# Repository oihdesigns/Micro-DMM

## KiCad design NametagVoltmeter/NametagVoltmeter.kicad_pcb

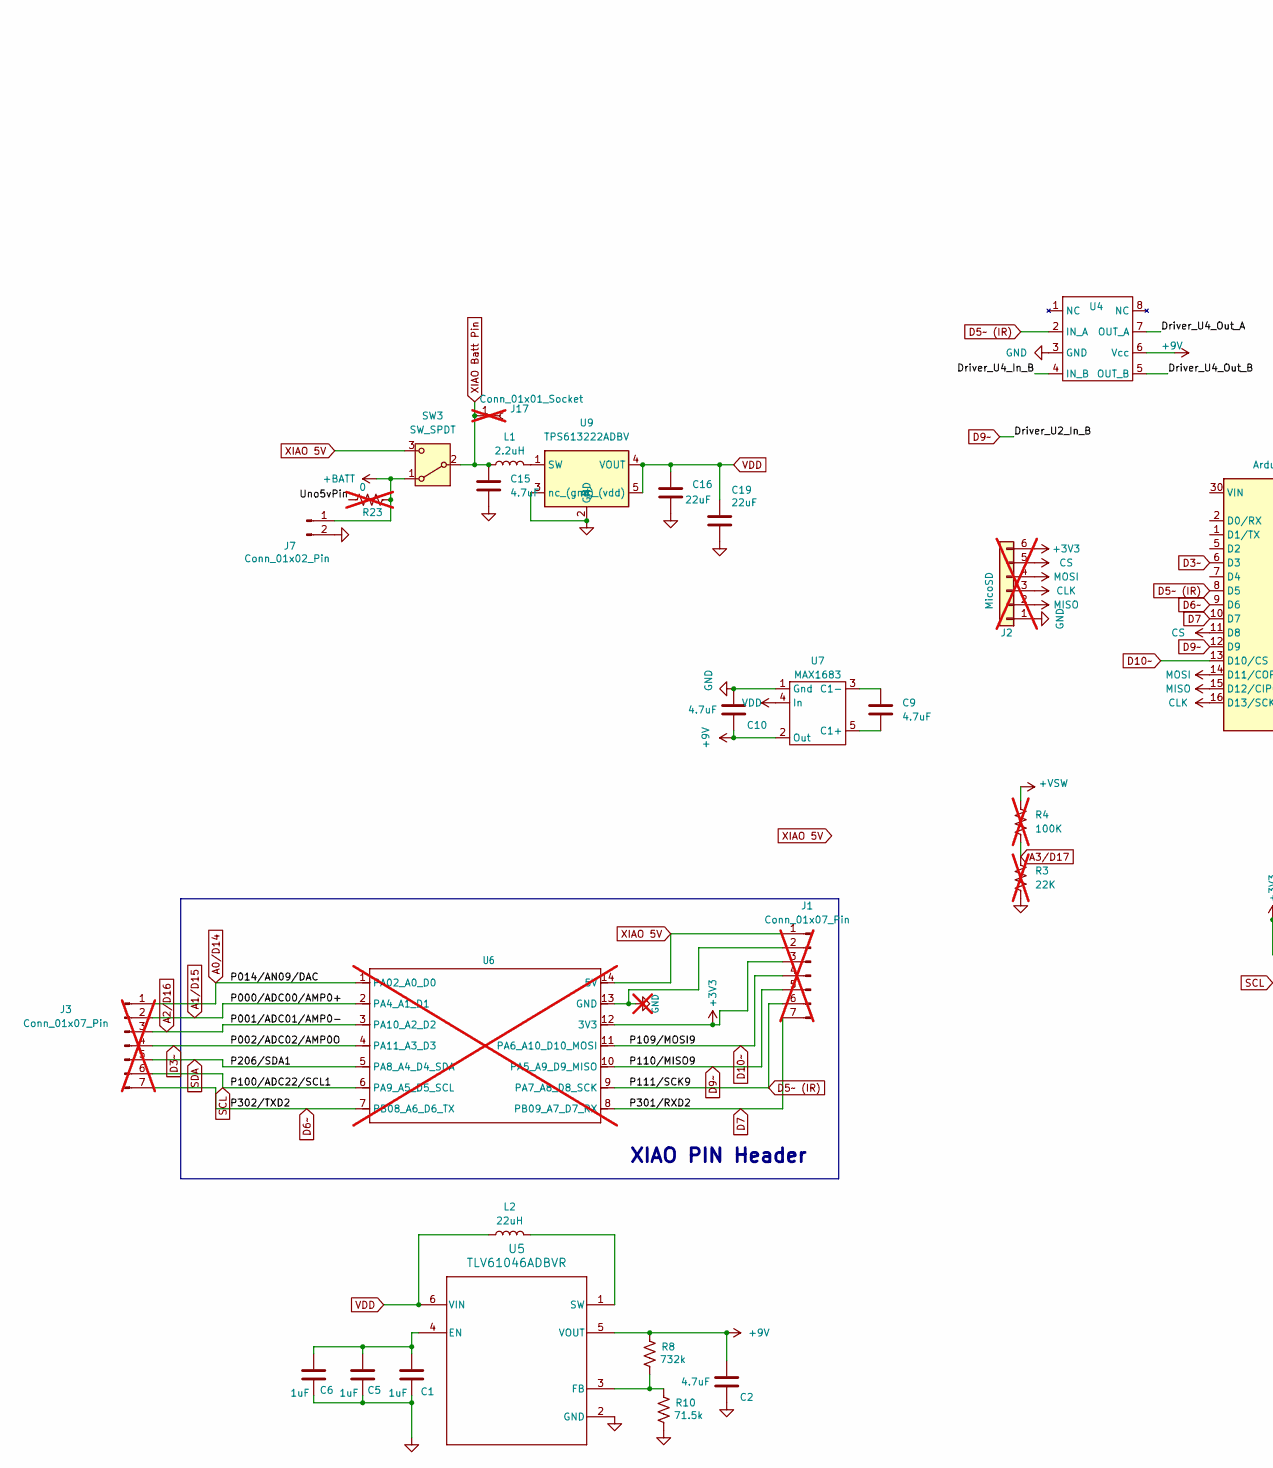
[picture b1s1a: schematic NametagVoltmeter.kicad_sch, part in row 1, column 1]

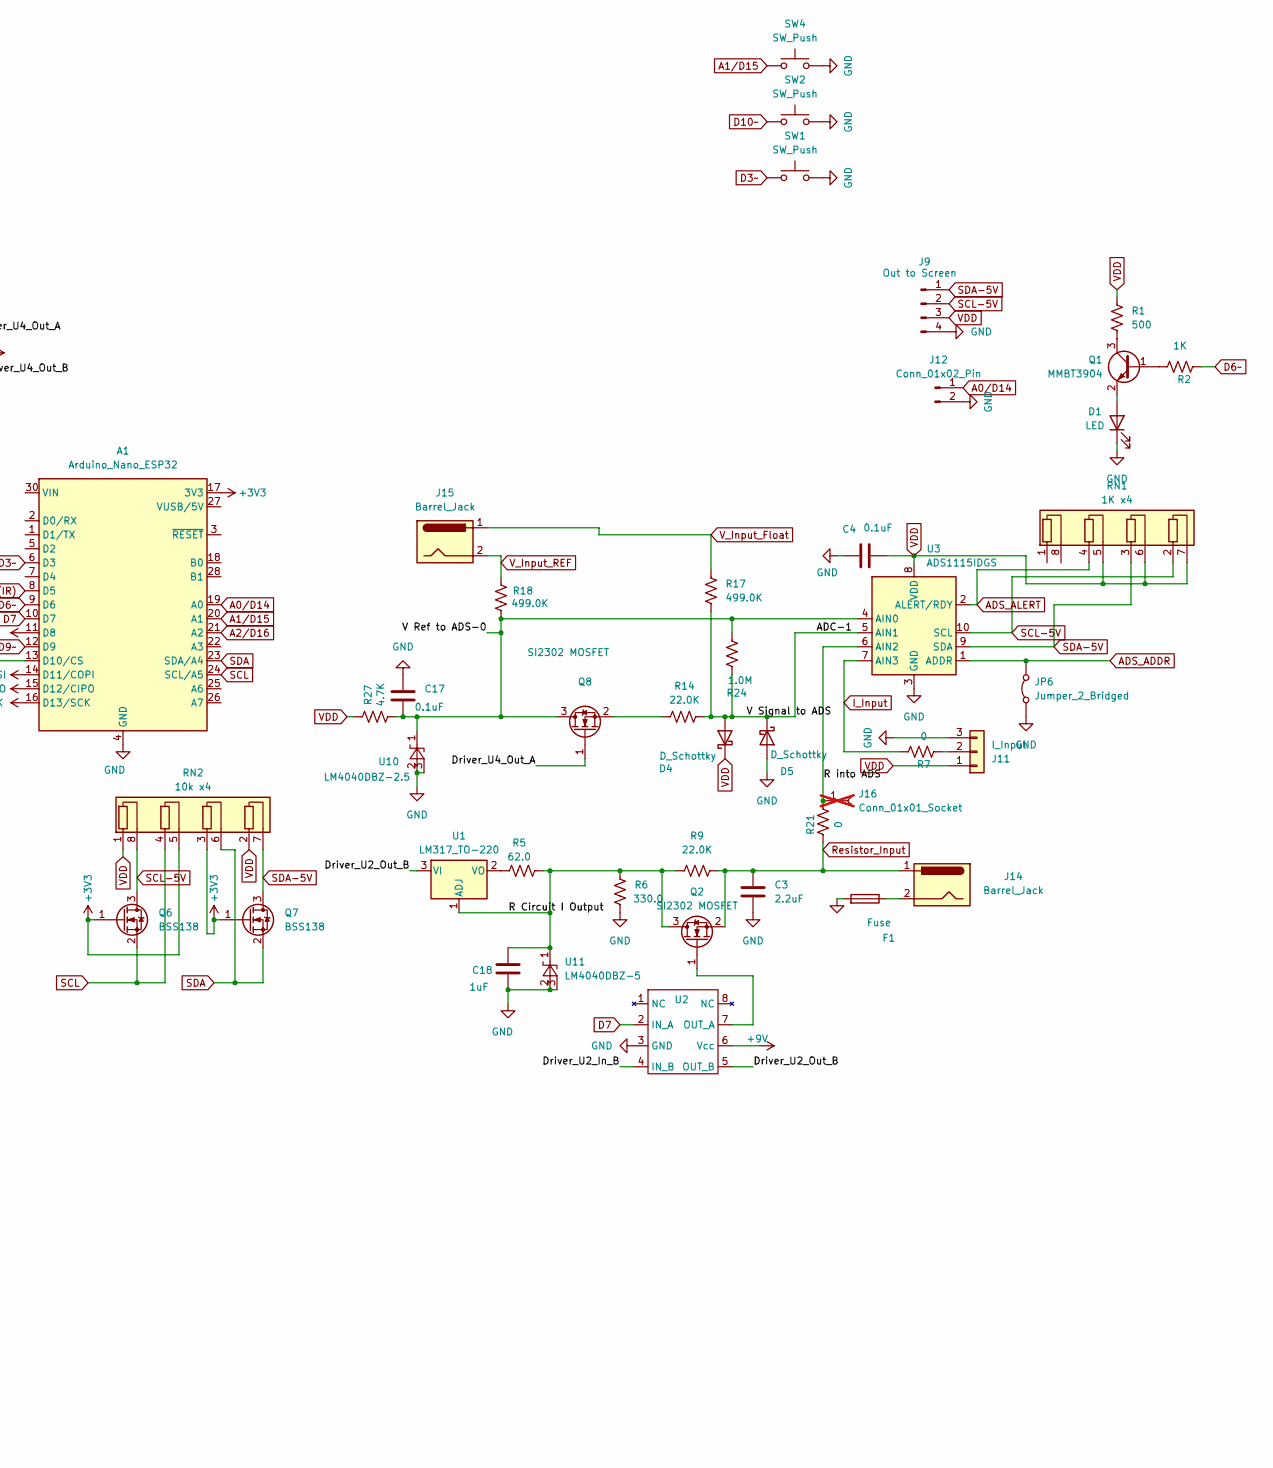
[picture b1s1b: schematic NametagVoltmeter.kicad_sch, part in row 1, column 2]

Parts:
A1: Arduino_Nano_ESP32; Arduino_Nano
C1, C5, C6, C18: 1uF; C_0805_2012Metric_Pad1.18x1.45mm_HandSolder
C2, C9, C10, C15: 4.7uF; C_0805_2012Metric_Pad1.18x1.45mm_HandSolder
C3: 2.2uF; C_0805_2012Metric_Pad1.18x1.45mm_HandSolder
C4, C17: 0.1uF; C_0805_2012Metric_Pad1.18x1.45mm_HandSolder
C16, C19: 22uF; C_0805_2012Metric_Pad1.18x1.45mm_HandSolder
D1: LED; LED_Luminus_MP-3030-1100_3.0x3.0mm
D4, D5: D_Schottky; D_SOD-123
F1: Fuse; Fuse_1206_3216Metric_Pad1.42x1.75mm_HandSolder
J1, J3: Conn_01x07_Pin; PinSocket_1x07_P2.54mm_Vertical; not fitted
J2: MicoSD; PinSocket_1x06_P2.54mm_Vertical; not fitted
J7, J12: Conn_01x02_Pin; PinSocket_1x02_P2.54mm_Vertical
J9: Out to Screen; PinSocket_1x04_P2.54mm_Vertical
J11: I_Input; PinSocket_1x03_P2.54mm_Vertical
J14, J15: Barrel_Jack; BarrelJack_Horizontal
J16, J17: Conn_01x01_Socket; PinSocket_1x01_P2.54mm_Vertical; not fitted
JP6: Jumper_2_Bridged; SolderJumper-2_P1.3mm_Bridged_Pad1.0x1.5mm
L1: 2.2uH; L_Murata_DFE201610P
L2: 22uH; L_Taiyo-Yuden_MD-5050
Q1: MMBT3904; SOT-23
Q2, Q8: SI2302 MOSFET; SOT-23
Q6, Q7: BSS138; SOT-23
R1: 500; R_0805_2012Metric_Pad1.20x1.40mm_HandSolder
R2: 1K; R_0805_2012Metric_Pad1.20x1.40mm_HandSolder
R3: 22K; R_0805_2012Metric_Pad1.20x1.40mm_HandSolder; not fitted
R4: 100K; R_0805_2012Metric_Pad1.20x1.40mm_HandSolder; not fitted
R5: 62.0; R_0805_2012Metric_Pad1.20x1.40mm_HandSolder
R6: 330.0; R_0805_2012Metric_Pad1.20x1.40mm_HandSolder
R7, R21: 0; R_0805_2012Metric_Pad1.20x1.40mm_HandSolder
R8: 732k; R_0805_2012Metric_Pad1.20x1.40mm_HandSolder
R9, R14: 22.0K; R_0805_2012Metric_Pad1.20x1.40mm_HandSolder
R10: 71.5k; R_0805_2012Metric_Pad1.20x1.40mm_HandSolder
R17, R18: 499.0K; R_0805_2012Metric_Pad1.20x1.40mm_HandSolder
R23: 0; R_0805_2012Metric_Pad1.20x1.40mm_HandSolder; not fitted
R24: 1.0M; R_0805_2012Metric_Pad1.20x1.40mm_HandSolder
R27: 4.7K; R_0805_2012Metric_Pad1.20x1.40mm_HandSolder
RN1: 1K x4; RESCAXS127P508X320X70-8N
RN2: 10k x4; RESCAXS127P508X320X70-8N
SW1, SW2, SW4: SW_Push; SW_SPST_CK_RS282G05A3
SW3: SW_SPDT; SW_Slide_SPDT_Angled_CK_OS102011MA1Q
U1: LM317_TO-220; SOT-223-3_TabPin2
U2, U4: IX4426N; SOIC-8_3.9x4.9mm_P1.27mm
U3: ADS1115IDGS; TSSOP-10_3x3mm_P0.5mm
U5: TLV61046ADBVR; SOT-23-6_Handsoldering
U6: not fitted
U7: MAX1683; SOT-23-5_HandSoldering
U9: TPS613222ADBV; SOT-23-5
U10: LM4040DBZ-2.5; SOT-23
U11: LM4040DBZ-5; SOT-23

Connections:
+3V3: A1.17 (3V3), J1.3, J2.6, Q6.1 (G), Q7.1 (G), RN2.3 (R3.1), RN2.5 (R2.2), U6.12 (3V3)
+9V: C2.1, C10.2, R8.1, U2.6 (Vcc), U4.6 (Vcc), U5.5 (VOUT), U7.2 (Out)
+BATT: J7.1, R23.2, SW3.1 (A)
+VSW: R4.2
/ADC-1: D4.2 (A), D5.1 (K), R14.2, R17.2, R24.1, U3.5 (AIN1)
/Driver_U2_Out_B: U1.3 (VI), U2.5 (OUT_B)
/Driver_U4_In_B: U4.4 (IN_B)
/Driver_U4_Out_A: Q8.1 (G), U4.7 (OUT_A)
/Driver_U4_Out_B: U4.5 (OUT_B)
/R Circuit I Output: C18.1, Q2.3 (D), R5.2, R6.2, R9.1, U1.1 (ADJ), U11.1 (K)
/R into ADS: J16.1, R21.1, U3.6 (AIN2)
/Uno5vPin: R23.1
/V Ref to ADS-0: C17.2, Q8.3 (D), R18.2, R24.2, R27.2, U3.4 (AIN0), U10.1 (K)
A0/D14: A1.19 (A0), J3.1, J12.1, U6.1 (PA02_A0_D0)
A1/D15: A1.20 (A1), J3.2, SW4.1, U6.2 (PA4_A1_D1)
A2/D16: A1.21 (A2), J3.3, U6.3 (PA10_A2_D2)
A3/D17: R3.2, R4.1
ADS_ADDR: JP6.2 (B), U3.1 (ADDR)
ADS_ALERT: RN1.4 (R2.1), U3.2 (ALERT/RDY)
CLK: A1.16 (D13/SCK), J2.3
CS: A1.11 (D8), J2.5
D3~: A1.6 (D3), J3.4, SW1.1, U6.4 (PA11_A3_D3)
D5~ (IR): A1.8 (D5), J1.6, U4.2 (IN_A), U6.9 (PA7_A8_D8_SCK)
D6~: A1.9 (D6), J3.7, R2.1, U6.7 (PB08_A6_D6_TX)
D7: A1.10 (D7), J1.7, U2.2 (IN_A), U6.8 (PB09_A7_D7_RX)
D9~: A1.12 (D9), J1.5, U2.4 (IN_B), U6.10 (PA5_A9_D9_MISO)
D10~: A1.13 (D10/CS), J1.4, SW2.1, U6.11 (PA6_A10_D10_MOSI)
GND: A1.4 (GND), A1.29 (GND), C1.2, C2.2, C3.2, C4.1, C5.2, C6.2, C10.1, C15.2, C16.2, C17.1, C18.2, C19.2, D1.1 (K), D5.2 (A), F1.2, J1.2, J2.1, J7.2, J9.4, J11.3, J12.2, JP6.1 (A), R3.1, R6.1, R10.2, SW1.2, SW2.2, SW4.2, U2.3 (GND), U3.3 (GND), U4.3 (GND), U5.2 (GND), U6.13 (GND), U7.1 (Gnd), U9.2 (GND), U9.3 (nc_(gnd)), U10.2 (A), U10.3 (nc_(gnd)), U11.2 (A), U11.3 (nc_(gnd))
I_Input: R7.1, U3.7 (AIN3)
MISO: A1.15 (D12/CIPO), J2.2
MOSI: A1.14 (D11/COPI), J2.4
unnamed: D1.2 (A), Q1.2 (E)
unnamed: F1.1, J14.2
unnamed: J11.2, R7.2
unnamed: Q1.1 (B), R2.2
unnamed: Q1.3 (C), R1.1
unnamed: Q2.1 (G), U2.7 (OUT_A)
unnamed: Q8.2 (S), R14.1
unnamed: R5.1, U1.2 (VO)
unnamed: C1.1, C5.1, C6.1, U5.4 (EN)
unnamed: R8.2, R10.1, U5.3 (FB)
unnamed: L2.2, U5.1 (SW)
unnamed: C9.2, U7.5 (C1+)
unnamed: C9.1, U7.3 (C1-)
unnamed: L1.2, U9.1 (SW)
Resistor_Input: C3.1, J14.1, Q2.2 (S), R9.2, R21.2
SCL: A1.24 (SCL/A5), J3.6, Q6.2 (S), RN2.4 (R2.1), U6.6 (PA9_A5_D5_SCL)
SCL-5V: J9.2, Q6.3 (D), RN1.2 (R4.1), RN2.8 (R1.2), U3.10 (SCL)
SDA: A1.23 (SDA/A4), J3.5, Q7.2 (S), RN2.6 (R3.2), U6.5 (PA8_A4_D4_SDA)
SDA-5V: J9.1, Q7.3 (D), RN1.3 (R3.1), RN2.7 (R4.2), U3.9 (SDA)
VDD: C4.2, C16.1, C19.1, D4.1 (K), J9.3, J11.1, L2.1, R1.2, R27.1, RN1.5 (R2.2), RN1.6 (R3.2), RN1.7 (R4.2), RN2.1 (R1.1), RN2.2 (R4.1), U3.8 (VDD), U5.6 (VIN), U7.4 (In), U9.4 (VOUT), U9.5 (nc_(vdd))
V_Input_Float: J15.1, R17.1
V_Input_REF: J15.2, R18.1
XIAO 5V: J1.1, SW3.3 (C), U6.14 (5V)
XIAO Batt Pin: C15.1, J17.1, L1.1, SW3.2 (B)

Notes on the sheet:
XIAO PIN Header

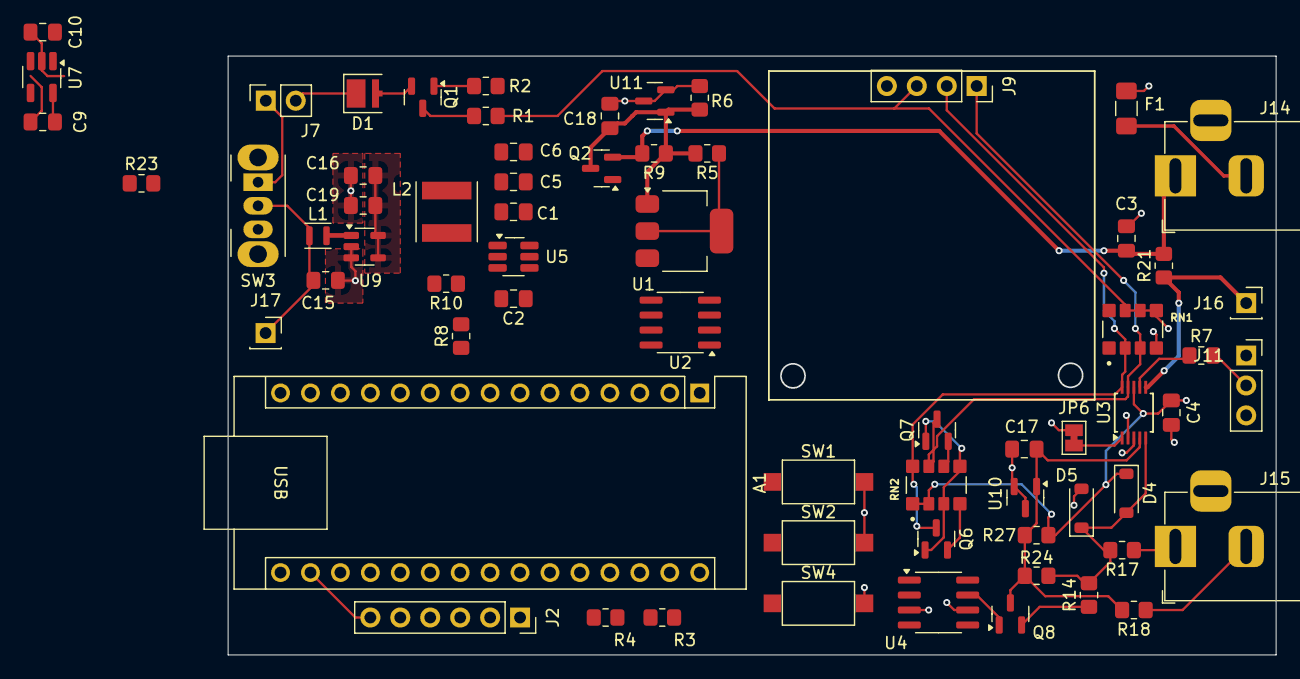
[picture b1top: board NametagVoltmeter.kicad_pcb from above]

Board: 4 copper layers, 88.9 x 50.8 mm, 66 parts (0 on the bottom side), 48 nets.

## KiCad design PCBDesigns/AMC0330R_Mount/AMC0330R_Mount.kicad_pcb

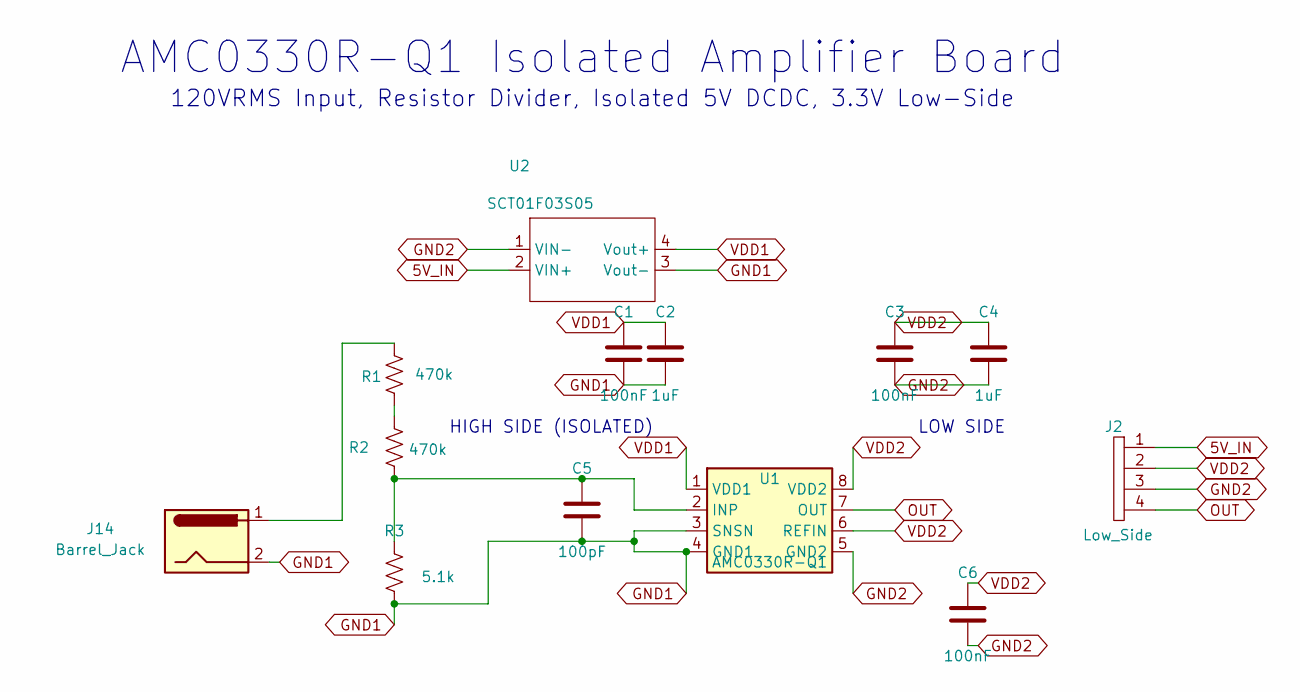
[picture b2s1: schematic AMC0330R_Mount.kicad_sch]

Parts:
C1, C3, C6: 100nF; C_0805_2012Metric_Pad1.18x1.45mm_HandSolder
C2, C4: 1uF; C_0805_2012Metric_Pad1.18x1.45mm_HandSolder
C5: 100pF; C_0805_2012Metric_Pad1.18x1.45mm_HandSolder
J2: Low_Side; PinHeader_1x04_P2.54mm_Vertical
J14: Barrel_Jack; BarrelJack_Horizontal
R1, R2: 470k; R_0805_2012Metric_Pad1.20x1.40mm_HandSolder
R3: 5.1k; R_0805_2012Metric_Pad1.20x1.40mm_HandSolder
U1: AMC0330R-Q1; SOIC-8_7.5x5.85mm_P1.27mm
U2: SCT01F03S05; Converter_DCDC_TRACO_TEA1-xxxx_THT

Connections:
5V_IN: J2.1, U2.2 (VIN+)
GND1: C1.2, C2.2, C5.2, J14.2, R3.2, U1.3 (SNSN), U1.4 (GND1), U2.3 (Vout-)
GND2: C3.2, C4.2, C6.2, J2.3, U1.5 (GND2), U2.1 (VIN-)
unnamed: J14.1, R1.1
unnamed: R1.2, R2.1
unnamed: C5.1, R2.2, R3.1, U1.2 (INP)
OUT: J2.4, U1.7 (OUT)
VDD1: C1.1, C2.1, U1.1 (VDD1), U2.4 (Vout+)
VDD2: C3.1, C4.1, C6.1, J2.2, U1.6 (REFIN), U1.8 (VDD2)

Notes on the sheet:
LOW SIDE
HIGH SIDE (ISOLATED)
AMC0330R-Q1 Isolated Amplifier Board
120VRMS Input, Resistor Divider, Isolated 5V DCDC, 3.3V Low-Side

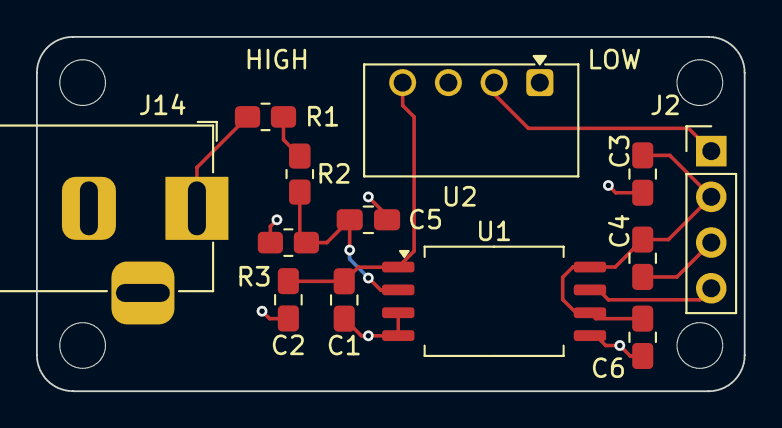
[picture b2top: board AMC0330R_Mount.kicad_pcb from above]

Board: 2 copper layers, 39.3 x 19.7 mm, 13 parts (0 on the bottom side), 9 nets.

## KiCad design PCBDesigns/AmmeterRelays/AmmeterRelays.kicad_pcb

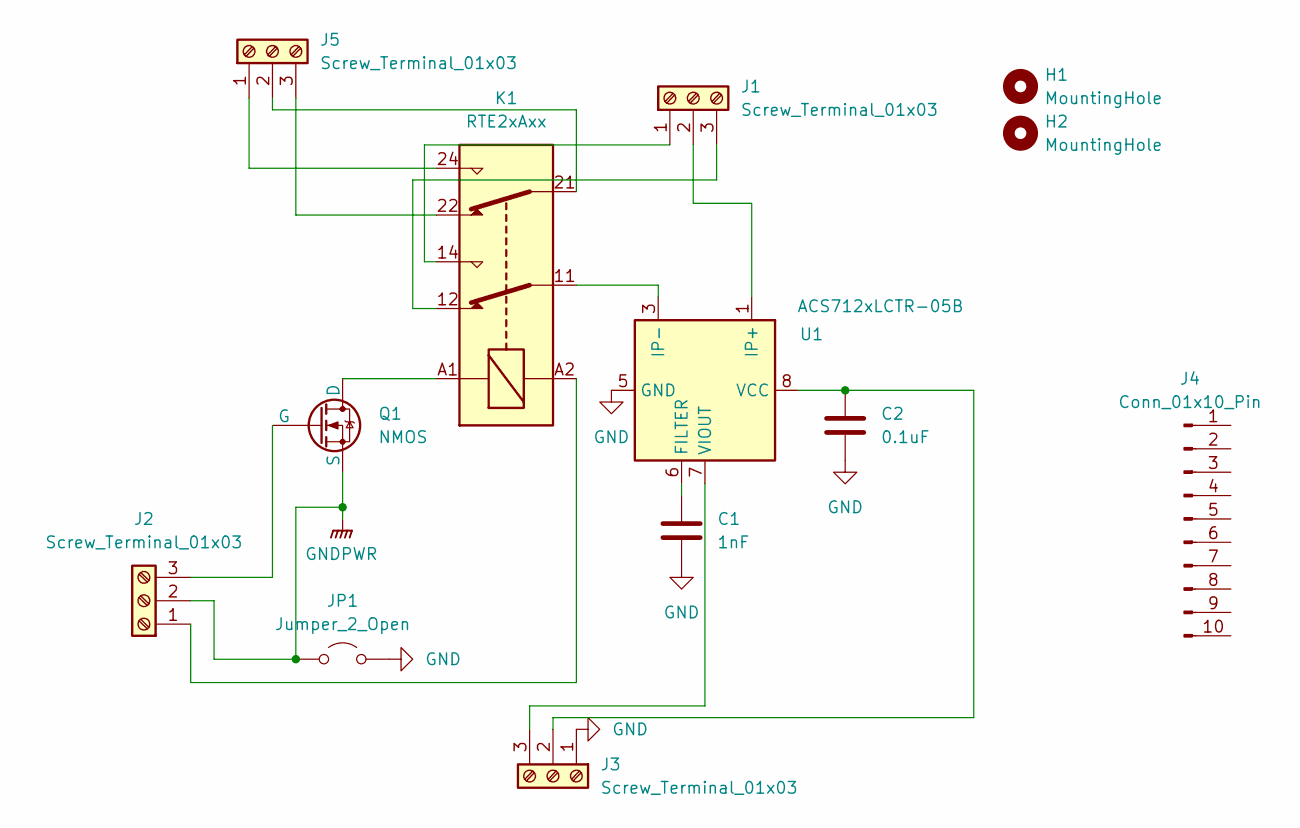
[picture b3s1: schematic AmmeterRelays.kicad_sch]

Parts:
C1: 1nF; C_0805_2012Metric_Pad1.18x1.45mm_HandSolder
C2: 0.1uF; C_0805_2012Metric_Pad1.18x1.45mm_HandSolder
H1, H2: MountingHole; MountingHole_3.2mm_M3_DIN965_Pad_TopBottom
J1, J5: Screw_Terminal_01x03; TerminalBlock_CUI_TB007-508-03_1x03_P5.08mm_Horizontal
J2, J3: Screw_Terminal_01x03; PinSocket_1x03_P2.54mm_Vertical
J4: Conn_01x10_Pin; PinHeader_1x20_P2.54mm_Vertical
JP1: Jumper_2_Open; PinHeader_1x02_P2.54mm_Vertical
K1: RTE2xAxx; Relay_DPDT_Schrack-RT2-FormC_RM5mm
Q1: NMOS; SOT-23-3
U1: ACS712xLCTR-05B; SOIC-8_3.9x4.9mm_P1.27mm

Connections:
GND: C1.2, C2.2, J3.1, JP1.2 (B), U1.5 (GND)
GNDPWR: J2.2, JP1.1 (A), Q1.2 (S)
unnamed: J1.1, K1.14
unnamed: J1.2, U1.1 (IP+), U1.2 (IP+)
unnamed: J1.3, K1.12
unnamed: J2.1, K1.A2
unnamed: J2.3, Q1.1 (G)
unnamed: C2.1, J3.2, U1.8 (VCC)
unnamed: J3.3, U1.7 (VIOUT)
unnamed: J5.1, K1.24
unnamed: J5.2, K1.21
unnamed: J5.3, K1.22
unnamed: K1.11, U1.3 (IP-), U1.4 (IP-)
unnamed: K1.A1, Q1.3 (D)
unnamed: C1.1, U1.6 (FILTER)

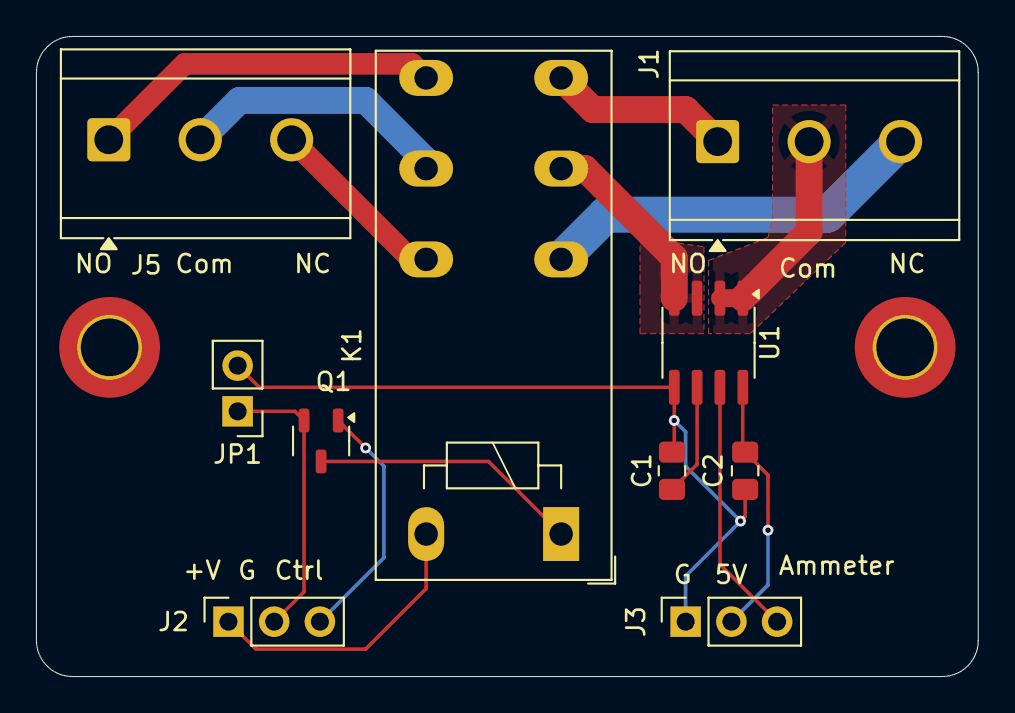
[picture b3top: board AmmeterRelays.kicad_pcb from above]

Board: 2 copper layers, 52.3 x 35.6 mm, 12 parts (0 on the bottom side), 15 nets.

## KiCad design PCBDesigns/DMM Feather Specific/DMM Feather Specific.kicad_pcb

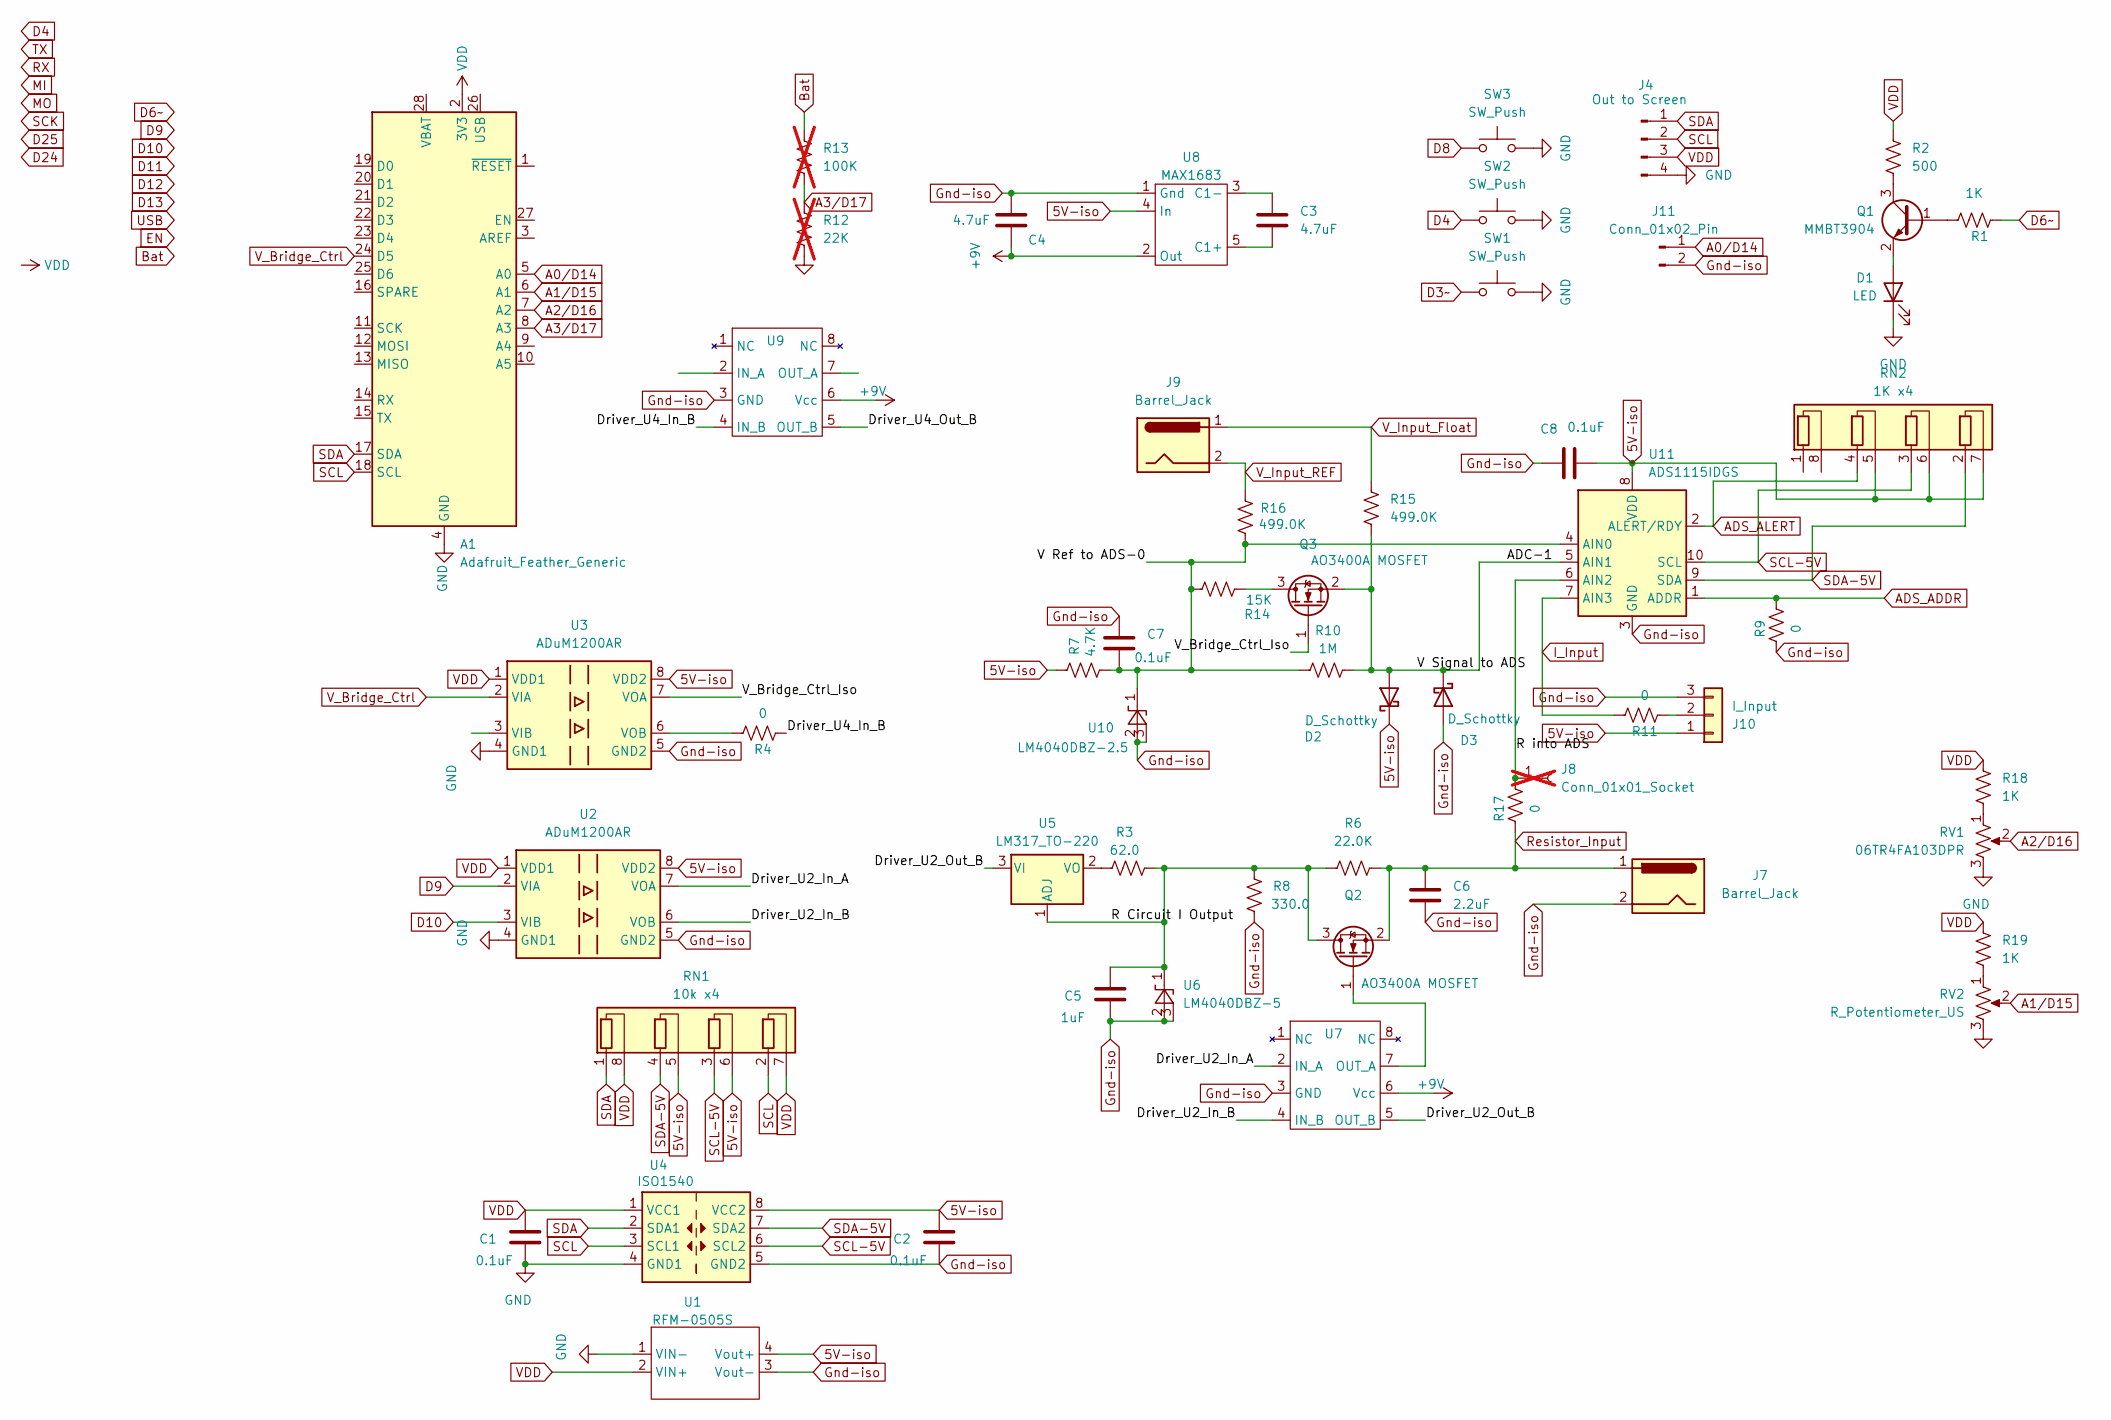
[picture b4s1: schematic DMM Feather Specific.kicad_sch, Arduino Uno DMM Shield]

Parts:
A1: Adafruit_Feather_Generic; Adafruit_Feather
C1, C2, C7, C8: 0.1uF; C_0805_2012Metric_Pad1.18x1.45mm_HandSolder
C3, C4: 4.7uF; C_0805_2012Metric_Pad1.18x1.45mm_HandSolder
C5: 1uF; C_0805_2012Metric_Pad1.18x1.45mm_HandSolder
C6: 2.2uF; C_0805_2012Metric_Pad1.18x1.45mm_HandSolder
D1: LED; LED_Luminus_MP-3030-1100_3.0x3.0mm
D2, D3: D_Schottky; D_SOD-123
J4: Out to Screen; PinSocket_1x04_P2.54mm_Vertical
J7, J9: Barrel_Jack; BarrelJack_Horizontal
J8: Conn_01x01_Socket; PinSocket_1x01_P2.54mm_Vertical; not fitted
J10: I_Input; PinSocket_1x03_P2.54mm_Vertical
J11: Conn_01x02_Pin; PinSocket_1x02_P2.54mm_Vertical
Q1: MMBT3904; SOT-23
Q2, Q3: AO3400A MOSFET; SOT-23
R1, R18, R19: 1K; R_0805_2012Metric_Pad1.20x1.40mm_HandSolder
R2: 500; R_0805_2012Metric_Pad1.20x1.40mm_HandSolder
R3: 62.0; R_0805_2012Metric_Pad1.20x1.40mm_HandSolder
R4, R9, R11, R17: 0; R_0805_2012Metric_Pad1.20x1.40mm_HandSolder
R6: 22.0K; R_0805_2012Metric_Pad1.20x1.40mm_HandSolder
R7: 4.7K; R_0805_2012Metric_Pad1.20x1.40mm_HandSolder
R8: 330.0; R_0805_2012Metric_Pad1.20x1.40mm_HandSolder
R10: 1M; R_0805_2012Metric_Pad1.20x1.40mm_HandSolder
R12: 22K; R_0805_2012Metric_Pad1.20x1.40mm_HandSolder; not fitted
R13: 100K; R_0805_2012Metric_Pad1.20x1.40mm_HandSolder; not fitted
R14: 15K; R_0805_2012Metric_Pad1.20x1.40mm_HandSolder
R15, R16: 499.0K; R_0805_2012Metric_Pad1.20x1.40mm_HandSolder
RN1: 10k x4; RESCAXS127P508X320X70-8N
RN2: 1K x4; RESCAXS127P508X320X70-8N
RV1: 06TR4FA103DPR; Potentiometer_ACP_CA6-VSMD_Vertical
RV2: R_Potentiometer_US; Potentiometer_ACP_CA6-VSMD_Vertical
SW1, SW2, SW3: SW_Push; SW_SPST_CK_RS282G05A3
U1: RFM-0505S; Converter_DCDC_TRACO_TEA1-xxxx_THT
U2, U3: ADuM1200AR; SOIC-8_3.9x4.9mm_P1.27mm
U4: ISO1540; SOIC-8_3.9x4.9mm_P1.27mm
U5: LM317_TO-220; SOT-223-3_TabPin2
U6: LM4040DBZ-5; SOT-23
U7, U9: IX4426N; SOIC-8_3.9x4.9mm_P1.27mm
U8: MAX1683; SOT-23-5_HandSoldering
U10: LM4040DBZ-2.5; SOT-23
U11: ADS1115IDGS; TSSOP-10_3x3mm_P0.5mm

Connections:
5V-iso: C2.1, C8.2, D2.1 (K), J10.1, R7.1, RN1.5 (R2.2), RN1.6 (R3.2), RN2.5 (R2.2), RN2.6 (R3.2), RN2.7 (R4.2), U1.4 (Vout+), U2.8 (VDD2), U3.8 (VDD2), U4.8 (VCC2), U8.4 (In), U11.8 (VDD)
+9V: C4.2, U7.6 (Vcc), U8.2 (Out), U9.6 (Vcc)
/ADC-1: D2.2 (A), D3.1 (K), Q3.2 (S), R10.2, R15.2, U11.5 (AIN1)
/Driver_U2_In_A: U2.7 (VOA), U7.2 (IN_A)
/Driver_U2_In_B: U2.6 (VOB), U7.4 (IN_B)
/Driver_U2_Out_B: U5.3 (VI), U7.5 (OUT_B)
/Driver_U4_In_B: R4.2, U9.4 (IN_B)
/Driver_U4_Out_B: U9.5 (OUT_B)
/R Circuit I Output: C5.1, Q2.3 (D), R3.2, R6.1, R8.2, U5.1 (ADJ), U6.1 (K)
/R into ADS: J8.1 (Pin_1_1), R17.1, U11.6 (AIN2)
/V Ref to ADS-0: C7.2, R7.2, R10.1, R14.2, R16.2, U10.1 (K), U11.4 (AIN0)
A0/D14: A1.5 (A0), J11.1
A1/D15: A1.6 (A1), RV2.2
A2/D16: A1.7 (A2), RV1.2
A3/D17: A1.8 (A3), R12.2, R13.1
ADS_ADDR: R9.1, U11.1 (ADDR)
ADS_ALERT: RN2.4 (R2.1), U11.2 (ALERT/RDY)
Bat: R13.2
D3~: SW1.1
D4: SW2.1
D5~ (IR): A1.24 (D5), U3.2 (VIA)
D6~: R1.1
D8: SW3.1
D9: U2.2 (VIA)
D10: U2.3 (VIB)
GND: A1.4 (GND), C1.2, D1.1 (K), J4.4, R12.1, RV1.3, RV2.3, SW1.2, SW2.2, SW3.2, U1.1 (VIN-), U2.4 (GND1), U3.4 (GND1), U4.4 (GND1)
Gnd-iso: C2.2, C4.1, C5.2, C6.2, C7.1, C8.1, D3.2 (A), J7.2, J10.3, J11.2, R8.1, R9.2, U1.3 (Vout-), U2.5 (GND2), U3.5 (GND2), U4.5 (GND2), U6.2 (A), U6.3 (nc_(gnd)), U7.3 (GND), U8.1 (Gnd), U9.3 (GND), U10.2 (A), U10.3 (nc_(gnd)), U11.3 (GND)
I_Input: R11.1, U11.7 (AIN3)
unnamed: D1.2 (A), Q1.2 (E)
unnamed: J10.2, R11.2
unnamed: Q1.1 (B), R1.2
unnamed: Q1.3 (C), R2.1
unnamed: Q2.1 (G), U7.7 (OUT_A)
unnamed: Q3.3 (D), R14.1
unnamed: R18.1, RV1.1
unnamed: R19.1, RV2.1
unnamed: R4.1, U3.6 (VOB)
unnamed: R3.1, U5.2 (VO)
unnamed: C3.2, U8.5 (C1+)
unnamed: C3.1, U8.3 (C1-)
Resistor_Input: C6.1, J7.1, Q2.2 (S), R6.2, R17.2
SCL: A1.18 (SCL), J4.2, RN1.2 (R4.1), U4.3 (SCL1)
SCL-5V: RN1.3 (R3.1), RN2.3 (R3.1), U4.6 (SCL2), U11.10 (SCL)
SDA: A1.17 (SDA), J4.1, RN1.1 (R1.1), U4.2 (SDA1)
SDA-5V: RN1.4 (R2.1), RN2.2 (R4.1), U4.7 (SDA2), U11.9 (SDA)
VDD: A1.2 (3V3), C1.1, J4.3, R2.2, R18.2, R19.2, RN1.7 (R4.2), RN1.8 (R1.2), U1.2 (VIN+), U2.1 (VDD1), U3.1 (VDD1), U4.1 (VCC1)
V_Input_Float: J9.1, R15.1
V_Input_REF: J9.2, R16.1

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
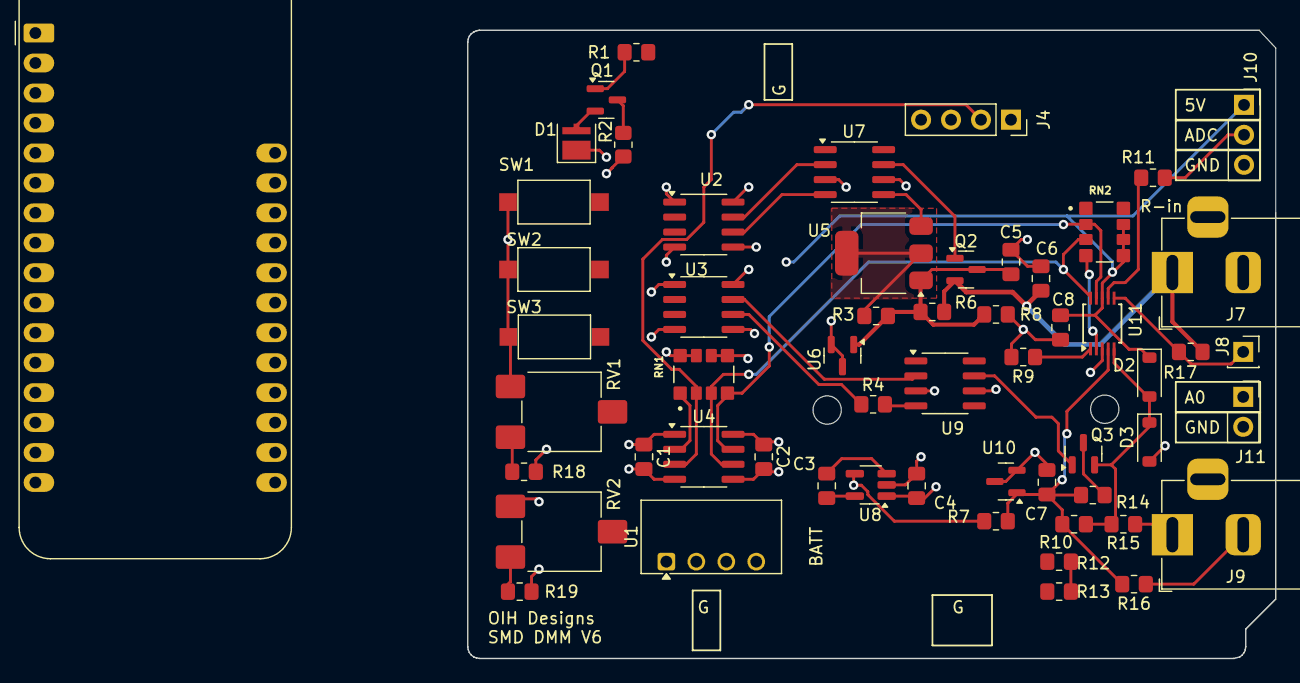
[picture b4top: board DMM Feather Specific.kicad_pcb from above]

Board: 4 copper layers, 68.5 x 53.2 mm, 57 parts (0 on the bottom side), 41 nets.
